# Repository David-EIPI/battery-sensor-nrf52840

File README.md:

# battery-sensor-nrf52840
PCB shared between several wireless sensors based on NRF52840 and powered by 18650 batteries

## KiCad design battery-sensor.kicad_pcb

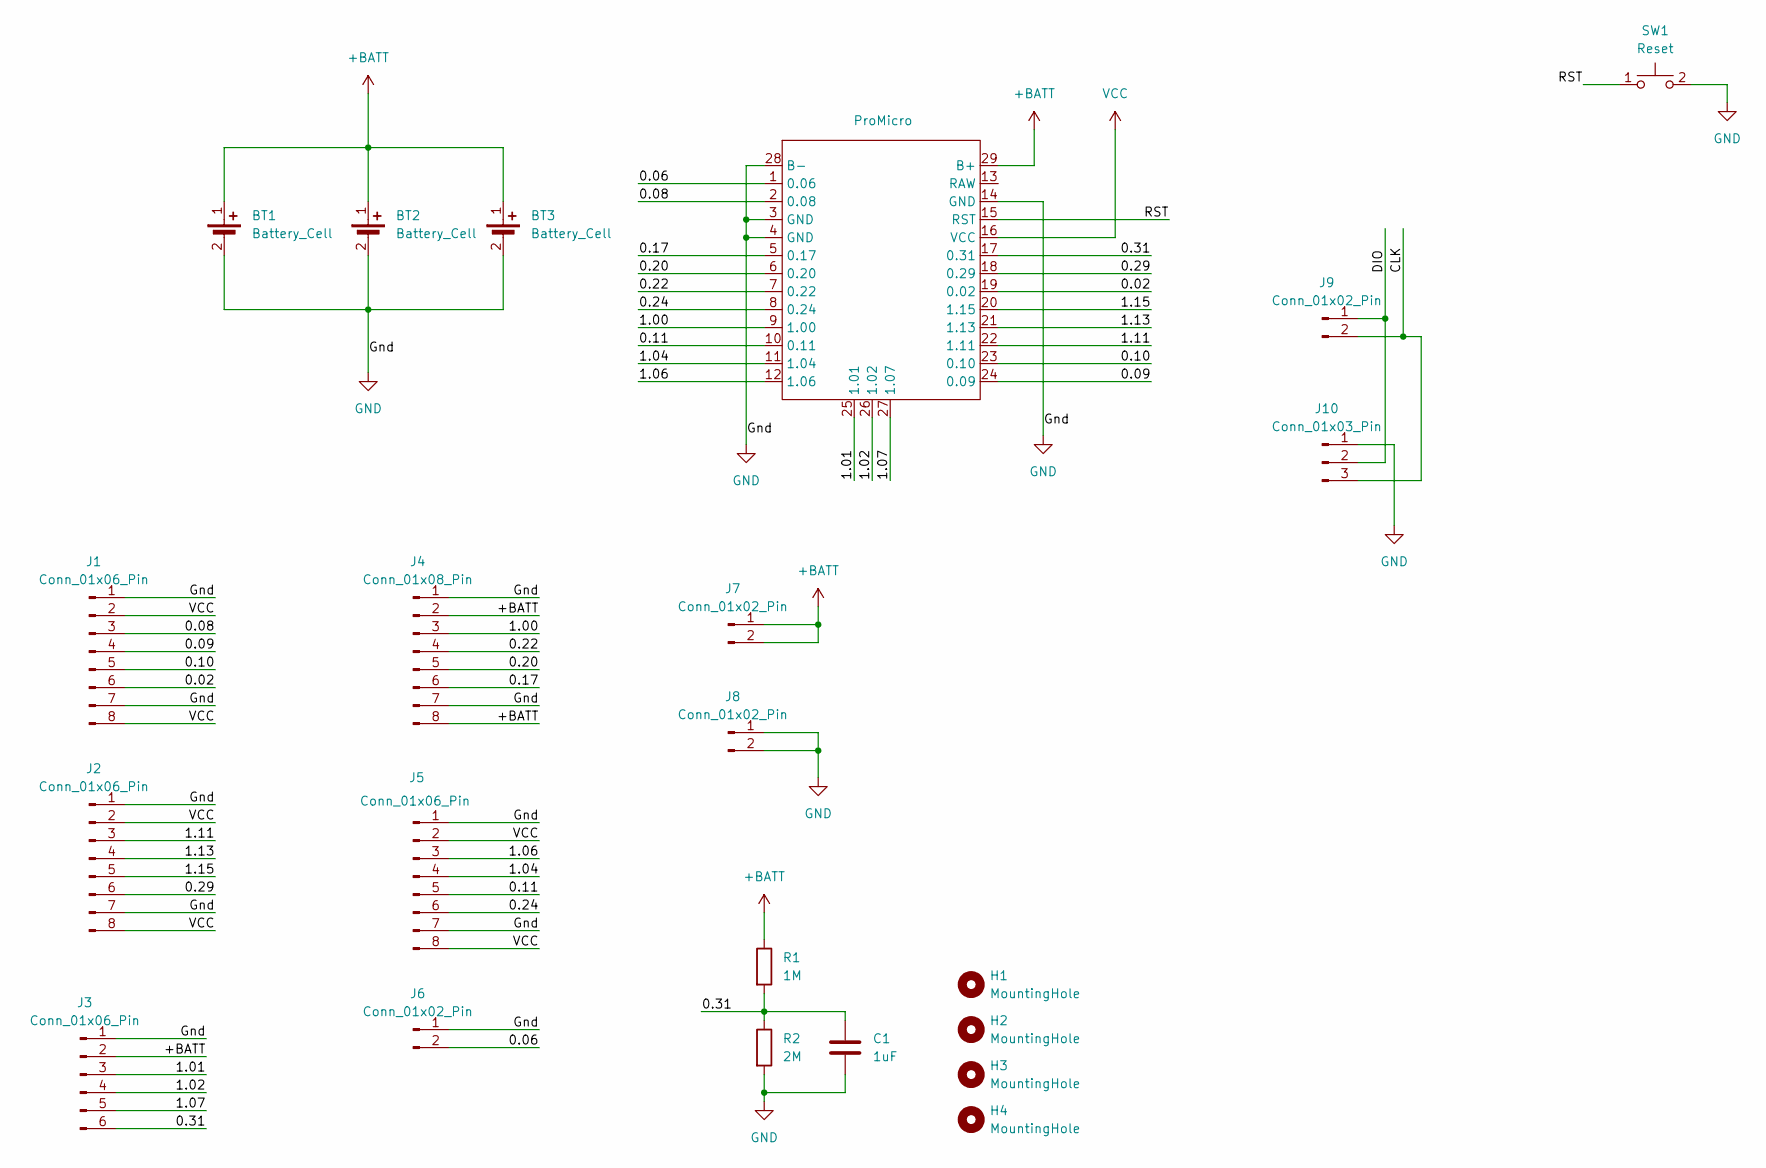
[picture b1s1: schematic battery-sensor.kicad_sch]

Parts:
BT1, BT2, BT3: Battery_Cell; 18650-edge-pins
C1: 1uF; C_0603_1608Metric_Pad1.08x0.95mm_HandSolder
H1, H2, H3, H4: MountingHole; MountingHole_3.5mm
J1, J2, J5: Conn_01x06_Pin; PinHeader_1x08_P2.54mm_Vertical
J3: Conn_01x06_Pin; PinHeader_1x06_P2.54mm_Vertical
J4: Conn_01x08_Pin; PinHeader_1x08_P2.54mm_Vertical
J6, J7, J8: Conn_01x02_Pin; PinHeader_1x02_P2.54mm_Vertical
J9: Conn_01x02_Pin; R_1206_3216Metric
J10: Conn_01x03_Pin; PinHeader_1x03_P2.54mm_Vertical
R1: 1M; R_0603_1608Metric_Pad0.98x0.95mm_HandSolder
R2: 2M; R_0603_1608Metric_Pad0.98x0.95mm_HandSolder
SW1: Reset; SW_Tactile_SPST_Angled_PTS645Vx39-2LFS
U1: ProMicro; ProMicro NRF52840

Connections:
+BATT: BT1.1 (+), BT2.1 (+), BT3.1 (+), J3.2, J4.2, J4.8, J7.1, J7.2, R1.1, U1.29 (B+)
/0.02: J1.6, U1.19 (0.02)
/0.06: J6.2, U1.1 (0.06)
/0.08: J1.3, U1.2 (0.08)
/0.09: J1.4, U1.24 (0.09)
/0.10: J1.5, U1.23 (0.10)
/0.11: J5.5, U1.10 (0.11)
/0.17: J4.6, U1.5 (0.17)
/0.20: J4.5, U1.6 (0.20)
/0.22: J4.4, U1.7 (0.22)
/0.24: J5.6, U1.8 (0.24)
/0.29: J2.6, U1.18 (0.29)
/0.31: C1.1, J3.6, R1.2, R2.1, U1.17 (0.31)
/1.00: J4.3, U1.9 (1.00)
/1.01: J3.3, U1.25 (1.01)
/1.02: J3.4, U1.26 (1.02)
/1.04: J5.4, U1.11 (1.04)
/1.06: J5.3, U1.12 (1.06)
/1.07: J3.5, U1.27 (1.07)
/1.11: J2.3, U1.22 (1.11)
/1.13: J2.4, U1.21 (1.13)
/1.15: J2.5, U1.20 (1.15)
/CLK: J9.2, J10.3
/DIO: J9.1, J10.2
/RST: SW1.1, U1.15 (RST)
GND: BT1.2 (-), BT2.2 (-), BT3.2 (-), C1.2, J1.1, J1.7, J2.1, J2.7, J3.1, J4.1, J4.7, J5.1, J5.7, J6.1, J8.1, J8.2, J10.1, R2.2, SW1.2, U1.3 (GND), U1.4 (GND), U1.14 (GND), U1.28 (B-)
VCC: J1.2, J1.8, J2.2, J2.8, J5.2, J5.8, U1.16 (VCC)

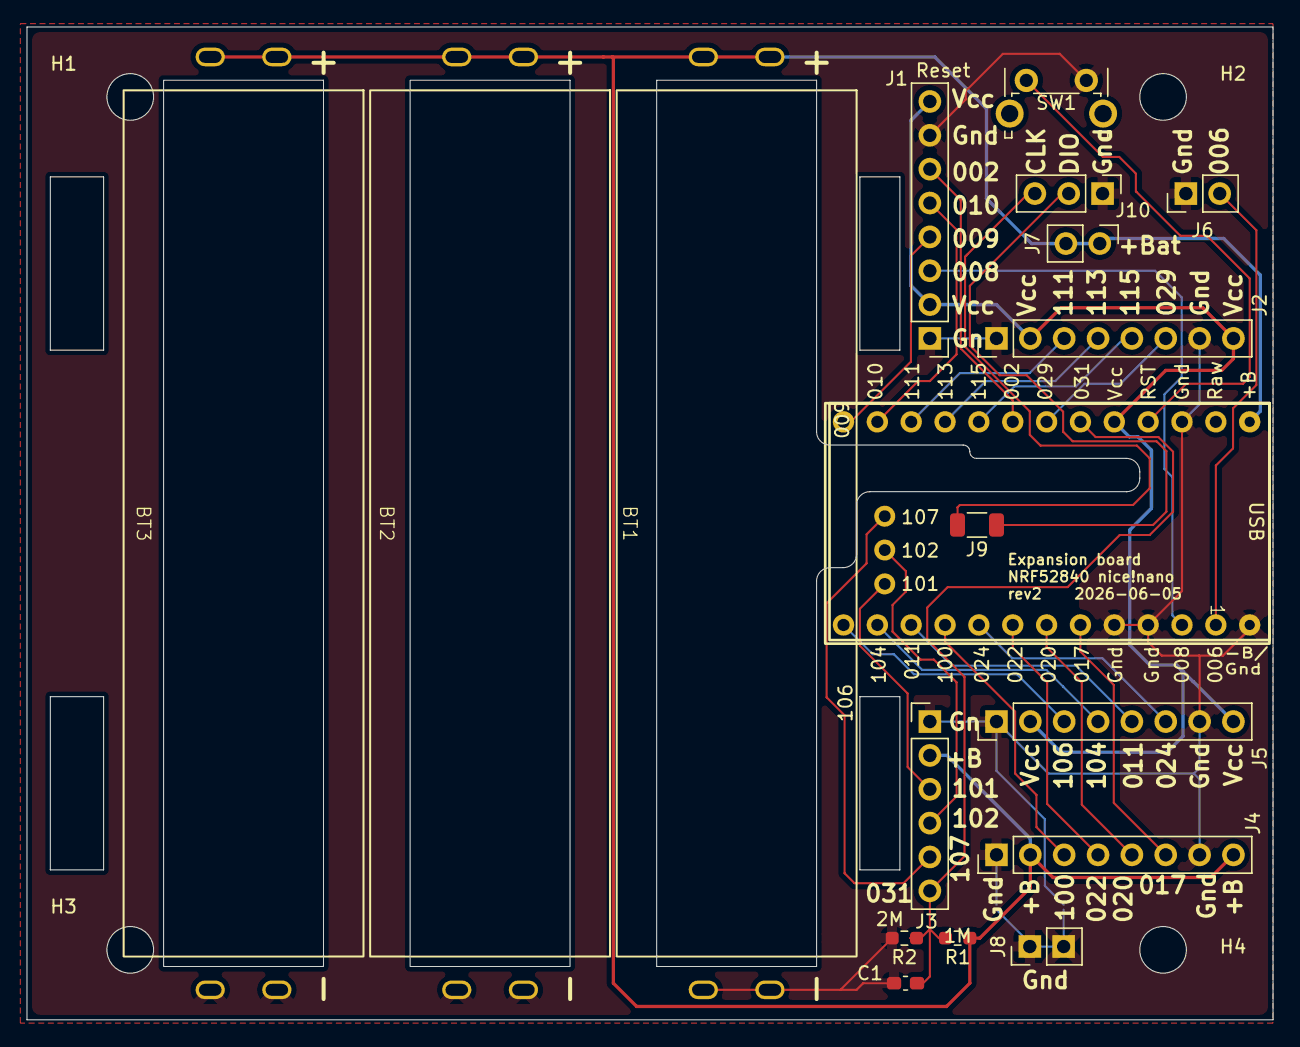
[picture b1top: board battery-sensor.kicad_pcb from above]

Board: 2 copper layers, 93.5 x 74.5 mm, 22 parts (1 on the bottom side), 27 nets.

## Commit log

2026-06-13 Initial upload.
    This board is intended as a common platform for battery powered sensors
    using clones (SuperMicro, ProMicro, etc) of the popular nice!nano NRF52840 board.
2026-06-16 Increase mounting hole size to account for small size variations of the plastic enclosures.
